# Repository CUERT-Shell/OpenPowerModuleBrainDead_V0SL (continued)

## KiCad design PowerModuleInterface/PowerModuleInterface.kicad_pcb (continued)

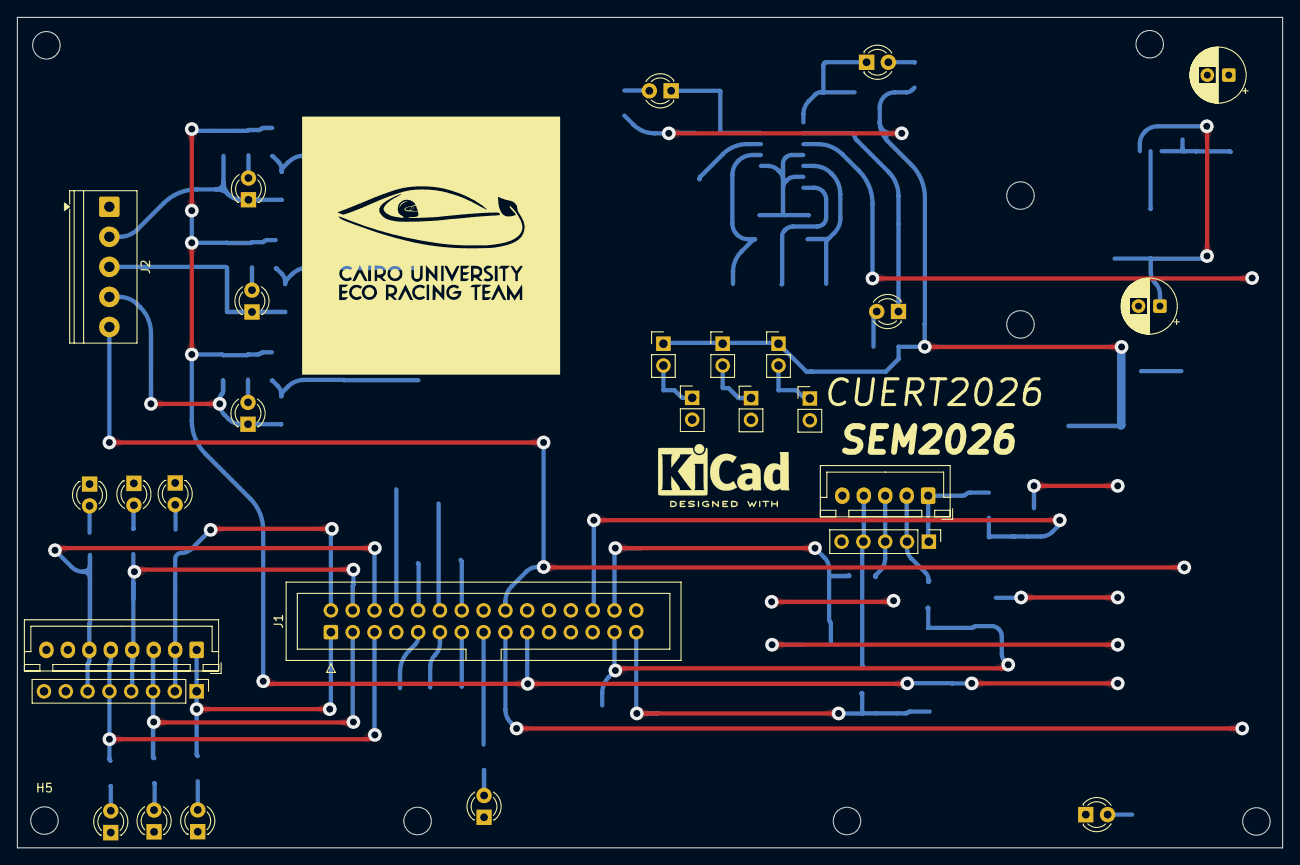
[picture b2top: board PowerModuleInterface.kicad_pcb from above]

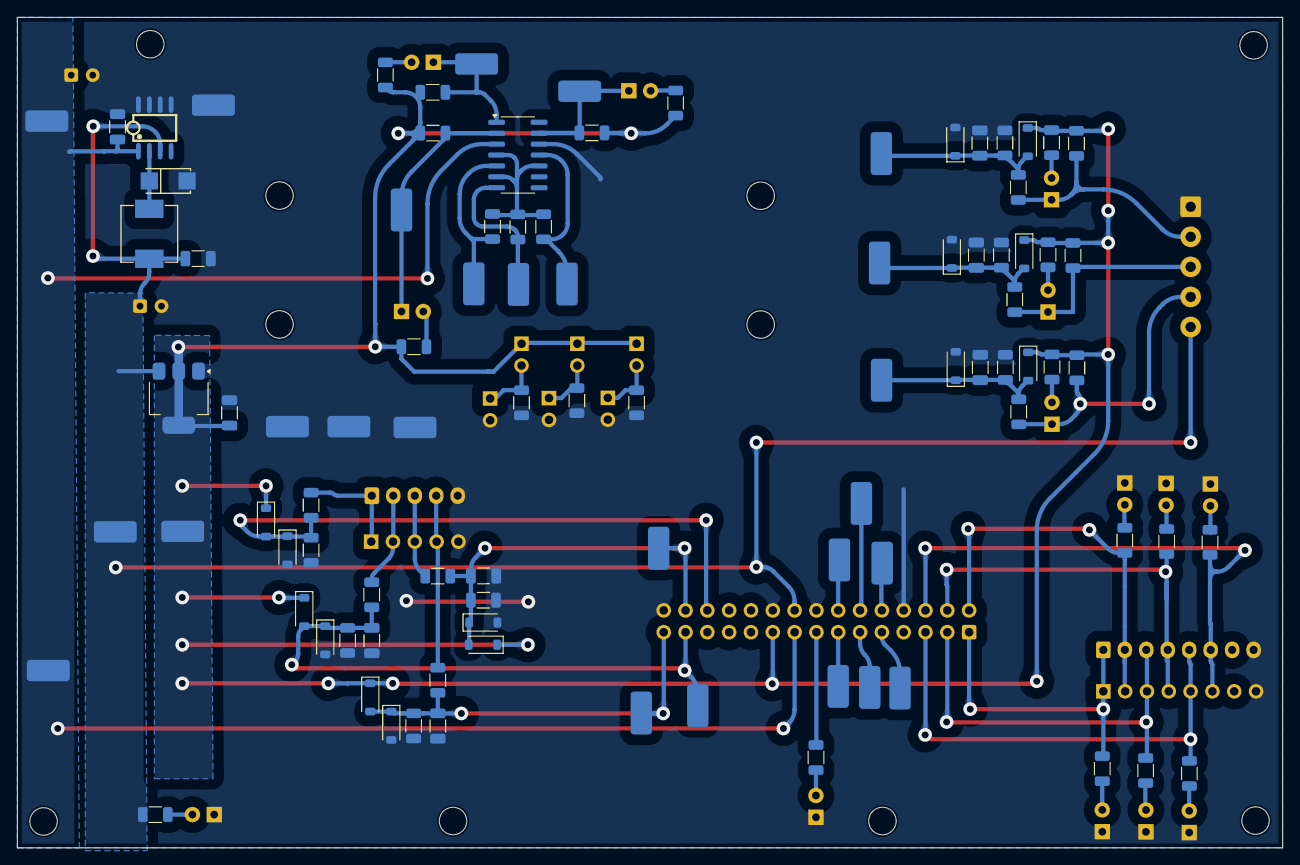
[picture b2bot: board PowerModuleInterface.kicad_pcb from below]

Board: 2 copper layers, 147.3 x 96.7 mm, 129 parts (94 on the bottom side), 56 nets.

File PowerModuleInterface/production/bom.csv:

Designator,Footprint,Quantity,Value,LCSC Part #
C1,CP_Radial_D6.3mm_P2.50mm,1,100uF-35V,
"C10, C11, C7",1206,3,47nF,
C2,1206,1,1u,
C3,CP_Radial_D6.3mm_P2.50mm,1,180uF-10V,
"C4, C5",1206,2,10u,
"C6, C8, C9",1206,3,100nF 50V,C24497
"D1, D11, D14, D21, D22, D23, D24, D25, D26, D27, D28, D29, D3, D6",LED_D3.0mm,14,LED,
"D10, D12, D13, D15, D16, D17, D18, D19, D20, D4, D5, D7, D8, D9",D_SOD-123,14,D_Schottky,C181204
D2,SMA_L4.3-W2.6-LS5.2-RD,1,SS34_C8678,C8678
"DRA1, DRA2",DinRailPCBClip_P15,2,DIN_Rail_Adapter,
J1,IDC-Header_2x15_P2.54mm_Vertical,1,Conn_02x15_Odd_Even,
"J10, J7",WirePad_2.5x5,2,A_HallCnd,
J11,WirePad_2.5x5,1,B_HallCnd,
"J12, J9",WirePad_2.5x5,2,C_HallCnd,
"J13, J16",WirePad_2.5x5,2,A_ZCD,
"J14, J17",WirePad_2.5x5,2,B_ZCD,
"J15, J18",WirePad_2.5x5,2,C_ZCD,
"J19, J20, J33, J34, J35, J36, J37, J38",WirePad_2.5x5,8,Conn_01x01_Pin,
J2,"TerminalBlock_Phoenix_PT-1,5-5-3.5-H_1x05_P3.50mm_Horizontal",1,Screw_Terminal_01x05,
"J21, J24",WirePad_2.5x5,2,A_PhaseCnd,
"J22, J25",WirePad_2.5x5,2,B_PhaseCnd,
"J23, J26",WirePad_2.5x5,2,C_PhaseCnd,
"J27, J28, J29, J30, J31, J32",PinHeader_1x02_P2.54mm_Vertical,6,Conn_01x02_Pin,
J3,JST_XH_B5B-XH-A_1x05_P2.50mm_Vertical,1,Conn_01x05,
J4,JST_XH_B8B-XH-A_1x08_P2.50mm_Vertical,1,Conn_01x08,
J5,PinHeader_1x08_P2.54mm_Vertical,1,Conn_01x08_Pin,
J6,PinHeader_1x05_P2.54mm_Vertical,1,Conn_01x05_Pin,
J8,WirePad_2.5x5,1,B_HallBCnd,
L1,IND-SMD_L7.1-W6.6_H5.0,1,SMMS0650-680M,C2894721
"R1, R12, R16, R23, R24, R25, R26, R27, R28, R29, R36, R37, R6",1206,13,1K,C113307
"R10, R20, R22, R3",1206,4,2.2K,
"R11, R15, R5",1206,3,4.7K,C17902
"R13, R17, R7",1206,3,470,C113307
"R14, R18, R8",1206,3,100,C113307
"R19, R2, R21, R9",1206,4,47K,
"R30, R31, R32",1206,3,4.7k,
"R33, R34, R35",1206,3,100k,
"R38, R39, R40",1206,3,2.2K,C113307
R4,1206,1,1k,
U1,SOIC-8_L5.0-W4.0-P1.27-LS6.0-BL,1,XL1509-5.0E1,C61063
U2,SOT-223-3_TabPin2,1,AMS1117-3.3,
U3,SOIC-14_3.9x8.7mm_P1.27mm,1,LM339,

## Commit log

2025-09-22 Init
2025-09-22 QuickFix
2025-09-22 Brief Documentation
